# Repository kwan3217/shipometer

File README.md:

# Ansible for Shipometer

## Before first boot

Use `rpi-imager`. 

### Older `rpi-image` (<2.0.3)

1. Get an image that does Debian 12 (Bookworm) not Debian 13 (Trixie)
    * Raspberry Pi OS (Other) -> Raspberry Pi OS (Legacy, 64-bit) Lite
2. Eject MicroSD card from fluttershy and insert it in SD card reader attached to Celestia. 
3. Edit settings
    * General
      * [x] Set Hostname: `fluttershy`.local
      * [x] Set username and password:
         * Username: `chrisj`
         * Password: ******
      * [ ] Configure wireless LAN
      * [x] Set locale settings:
         * Time Zone: `America/Chicago` or as appropriate 
         * Keyboard layout: `us`
    * Services
       * [x] Enable SSH
          * ( ) Use password authentication
          * (*) Allow public-key authentication only
             * Set authorized_keys for `chrisj`: `<copy and paste from first line of /home/chrisj/.ssh/id_rsa.pub>` 
    * Options
      * [ ] Play sound when finished
      * [x] Eject media when finished
      * [ ] Enable telemetry

### Newer `rpi-image` (2.0.3)
1. Select the device type -- Raspberry Pi 5 for the current `fluttershy`
2. Raspberry Pi OS (Other) -> Raspberry Pi OS (Legacy, 64-bit) Lite
3. Insert and select the correct medium -- it is often already mounted
   as `/media/chrisj/devicename`. It is CRITICALLY IMPORTANT to get this right 
   -- check that the file size matches what is expected, and that it isn't
   one of your existing drives on the host filesystem. The check box [x] Exclude System Drives
   helps with this.
4. Set the hostname `fluttershy` not `fluttershy.local` or `fluttershy.kwansystems.org`
5. Set the capital city, time zone, and keyboard layout.
6. Set the user name `chrisj` and the password `<SECRET>`
7. Skip wifi for now
8. Enable SSH
   * ( ) Use Password Authentication
   * (*) Use public key authentication
      * Set authorized_keys for `chrisj`: `<copy and paste from first line of /home/chrisj/.ssh/id_rsa.pub>` 

### Write the image
Continue until the program writes the image on the card. Writing the image will take a few minutes.

## SSH host identity
Eject the card but then plug it back into the host. Run this:

```
sudo cp -av /mnt/big/backups/fluttershy/2025-12-15/etc/ssh/ssh_host_* /media/chrisj/rootfs/etc/ssh/
```

Edit the file `/media/chrisj/rootfs/usr/lib/raspberrypi-sys-mods/firstboot` and comment out the lines about
recalculating the host identity:
```
main () {
  get_variables

  # whiptail --infobox "Generating SSH keys..." 20 60
  # regenerate_ssh_host_keys
```

## Boot new card in Fluttershy
Eject the card again, move it back to Fluttershy, and boot it.

Unmount and remove the card from the host and install it in a powered-off or red light Raspberry Pi 5.
Start it back up and wait for it to respond to pings. The router (Megumu)
knows Fluttershy's MAC address and will assign it the known IP `192.168.217.102`
and name `fluttershy.kwansystems.org`

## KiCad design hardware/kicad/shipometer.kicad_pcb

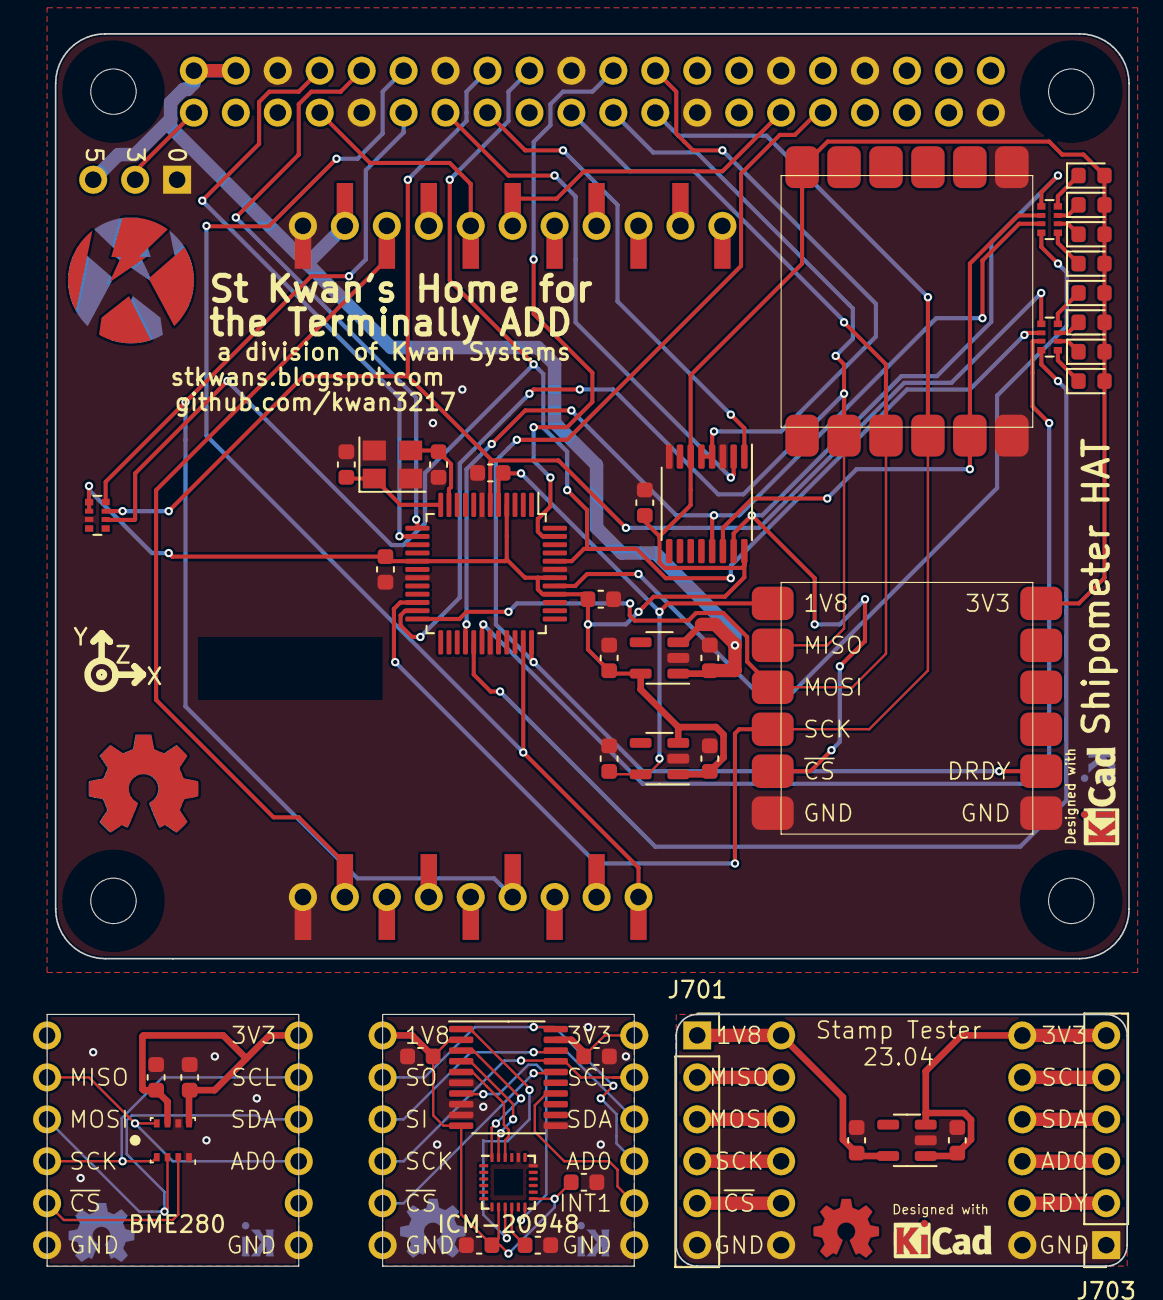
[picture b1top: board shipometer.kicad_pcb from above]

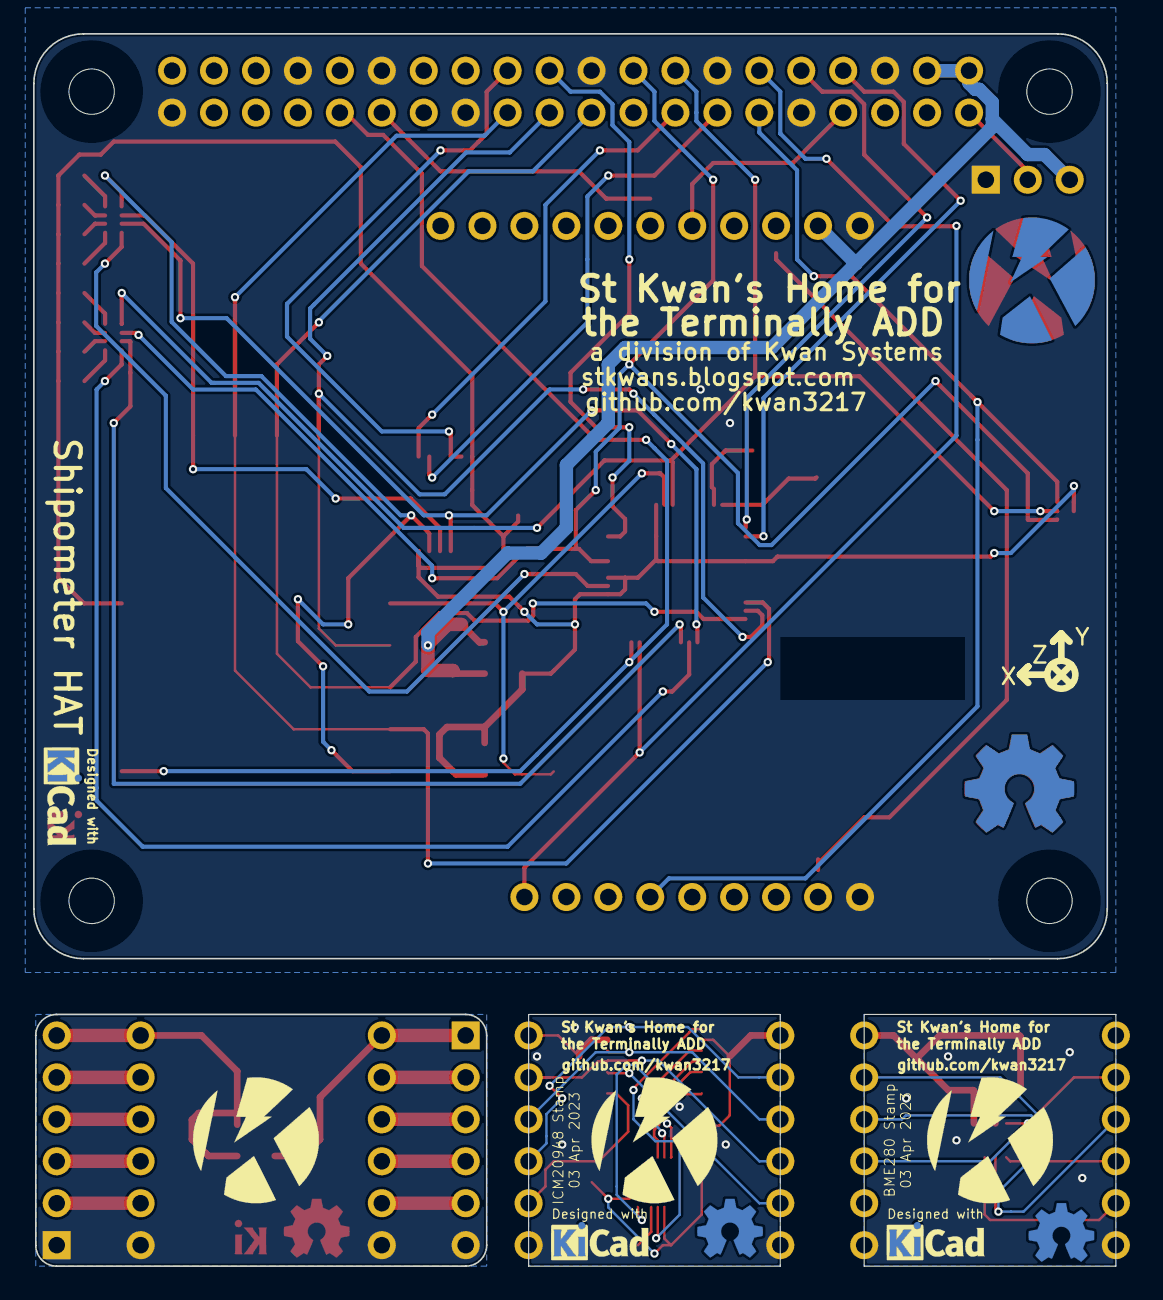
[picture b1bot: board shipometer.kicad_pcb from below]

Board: 2 copper layers, 65.5 x 74.6 mm, 66 parts (10 on the bottom side), 69 nets.

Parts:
C116, C206, C208, C401, C405, C501, C505, C605, C617, C640, C801, C805: 1uF; C_0603_1608Metric
C302, C308, C310, C313, C319: 100nF; C_0603_1608Metric
C611, C612: 22pF; C_0603_1608Metric
D101, D103, D104: White; LED_0603_1608Metric
D106: Blue; LED_0603_1608Metric
D129: Red; LED_0603_1608Metric
D130: Green; LED_0603_1608Metric
D141, D144: Yellow; LED_0603_1608Metric
G101: Axis
G102, G105: KwanSystems; StKwansSoldermask
G103, G107, G202, G302, G702: Designed with; Symbol_KiCAD-Logo_CopperAndSilkScreenTop_small
G104, G106: OSHW; OSHW-Symbol_6.7x6mm_SolderMask
G201, G301, G701: github.com/kwan3217; KWAN_CIRCLE
G203, G303, G703: OSHW; OSHW-Symbol_4x3.6mm_SolderMask
J101: Raspberry_Pi_40; PiHAT_NoSlot_Narrow
J102: Conn_01x03; PinHeader_1x03_P2.54mm_Horizontal
J104: ICM20948; StampPad
J105: BME280; StampPad
J106: ZED-F9R
J201, J301: Stamp
J701, J703: Conn_01x06_Pin; PinSocket_1x06_P2.54mm_Vertical
J702, J704: Conn_01x06_Pin; PinHeader_1x06_P2.54mm_Vertical
R101, R102: 330; R_Array_Convex_4x0402
R103: 10k; R_Array_Convex_4x0402
U102: 74LS138; TSSOP-16_4.4x5mm_P0.65mm
U201: BME280; Bosch_LGA-8_2.5x2.5mm_P0.65mm_ClockwisePinNumbering
U301: ICM-20948; InvenSense_QFN-24_3x3mm_P0.4mm
U302: TXS0108EPW; TSSOP-20_4.4x6.5mm_P0.65mm
U401: TCR2EF 3.3V; SOT-23-5
U501, U801: TCR2EF 1.8V; SOT-23-5
U601: LPC210x; LQFP-48_7x7mm_P0.5mm
Y601: 12MHz; Crystal_SMD_Abracon_ABM8G-4Pin_3.2x2.5mm

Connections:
3V3: J106.3 (3V3), J106.13 (3V3)
+1V8: C505.1, C605.1, J104.1 (1V8), U501.5 (OUT), U601.5 (VDD(1V8))
+3.3VP: J101.1 (3V3), J102.2
+3V3: C116.1, C405.1, C501.1, C617.1, C640.1, D101.2 (A), D103.2 (A), D104.2 (A), D106.2 (A), D129.2 (A), D130.2 (A), D141.2 (A), D144.2 (A), J104.12 (3V3), J105.12 (3V3), R103.1 (4), R103.2 (4), U102.6 (E3), U102.16 (VCC), U401.5 (OUT), U501.1 (IN), U501.3 (EN), U601.4 (VBAT), U601.17 (VDD(3V3)), U601.40 (VDD(3V3)), U601.42 (VDDA)
+5V: C401.1, J101.2 (5V), J101.4 (5V), J102.3, J106.2 (5V), U401.1 (IN), U401.3 (EN)
/BOOTSTRAP-: D144.1 (K), R102.7 (5)
/CS_A0: J101.15 (GPIO22_(GEN3)), U102.1 (A0)
/CS_A1: J101.13 (GPIO27_(GEN2)), U102.2 (A1)
/DRDY-: D129.1 (K), R102.5
/DRDY_6D: J101.31 (GPIO6), J104.8 (DRDY), U601.36 ((CTS1/CAP1.1/AD0.4)P0.11)
/DRDY_MAG: J101.22 (GPIO25_(GEN6)), U601.47 ((CAP1.2/SCL1)P0.17)
/DRDY_MAG-: D130.1 (K), R102.6 (5)
/GPS_RX: J101.7 ((TX3)_GPIO4), J106.5 (RX/MOSI)
/GPS_TX: J101.29 ((RX3)_GPIO5), J106.6 (TX/MISO)
/GPS_~RESET: J101.11 (GPIO17_(GEN0)), J106.17 (~RESET), R103.8 (5)
/IMU/INT1_1V8: U301.12 (INT1), U302.7 (A6)
/IMU/INT1_3V3: J301.8 (INT1), U302.14 (B6)
/IMU/MISO_1V8: U301.9 (SDO/AD0), U302.1 (A1)
/IMU/MISO_3V3: J301.2 (MISO), J301.9 (AD0), U302.20 (B1)
/IMU/MOSI_1V8: U301.24 (SDA/SDI), U302.3 (A2)
/IMU/MOSI_3V3: J301.3 (MOSI), J301.10 (SDA), U302.18 (B2)
/IMU/Q_1V8: C302.1, C308.1, C313.1, J301.1 (1V8), U301.8 (VDDIO), U301.13 (VDD), U302.2 (VCCA), U302.10 (OE)
/IMU/Q_3V3: C319.1, J301.12 (3V3), U302.19 (VCCB)
/IMU/Q_GND: C302.2, C308.2, C310.2, C313.2, C319.2, J301.6 (GND), J301.7 (GND), U301.18 (GND), U301.20 (GND), U302.6 (A5), U302.8 (A7), U302.9 (A8), U302.11 (GND)
/IMU/SCK_1V8: U301.23 (SCL/SCLK), U302.4 (A3)
/IMU/SCK_3V3: J301.4 (SCK), J301.11 (SCL), U302.17 (B3)
/IMU/~CS_1V8: U301.22 (~CS), U302.5 (A4)
/IMU/~CS_3V3: J301.5 (~CS), U302.16 (B4)
/LPC_RESET-: D106.1 (K), R102.8 (5)
/LPC_RX: J101.8 ((TX0)_GPIO14), U601.14 ((RXD0/MAT3.2)P0.1)
/LPC_TX: J101.10 ((RX0)_GPIO15), U601.13 ((TXD0/MAT3.1)P0.0)
/LPC_~BOOTSTRAP: J101.18 (GPIO24_(GEN5)), R102.2 (4), R103.6 (5), U601.44 ((DCD1/SCK1/EINT1)P0.14)
/LPC_~RESET: J101.16 (GPIO23_(GEN4)), R102.1 (4), R103.7 (5), U601.6 (~RST)
/MISO_3V3: J101.21 ((SPI_MISO)_GPIO9), J104.2 (MISO), J105.2 (MISO), U601.23 ((MISO0/MAT0.1)P0.5)
/MOSI_3V3: J101.19 ((SPI_MOSI)_GPIO10), J104.3 (MOSI), J105.3 (MOSI), U601.24 ((MOSI0/CAP0.2)P0.6)
/PPS: J101.12 (GPIO18_(GEN1)), J106.20 (PPS), U601.35 ((RTS1/CAP1.0/AD0.3)P0.10)
/PPS-: D141.1 (K), R101.5
/Pressure/MISO: J201.2 (MISO), J201.9 (AD0), U201.5 (SDO)
/Pressure/MOSI: J201.3 (MOSI), J201.10 (SDA), U201.3 (SDI)
/Pressure/Q_3V3: C206.1, C208.1, J201.12 (3V3), U201.6 (VDDIO), U201.8 (VDD)
/Pressure/Q_GND: C206.2, C208.2, J201.6 (GND), J201.7 (GND), U201.1 (GND), U201.7 (GND)
/Pressure/SCK: J201.4 (SCK), J201.11 (SCL), U201.4 (SCK)
/Pressure/~CS: J201.5 (~CS), U201.2 (CSB)
/SCK_3V3: J101.23 ((SPI_SCLK)_GPIO11), J104.4 (SCK), J105.4 (SCK), U601.22 ((SCK0/CAP0.1)P0.4)
/Stamp Tester/Q_1V8: C805.1, J701.1, J702.1, U801.5 (OUT)
/Stamp Tester/Q_3V3: C801.1, J703.6, J704.6, U801.1 (IN), U801.3 (EN)
/Stamp Tester/Q_AD0: J703.3, J704.3
/Stamp Tester/Q_DRDY: J703.2, J704.2
/Stamp Tester/Q_GND: C801.2, C805.2, J701.6, J702.6, J703.1, J704.1, U801.2 (GND)
/Stamp Tester/Q_MISO: J701.2, J702.2
/Stamp Tester/Q_MOSI: J701.3, J702.3
/Stamp Tester/Q_SCK: J701.4, J702.4
/Stamp Tester/Q_SCL: J703.5, J704.5
/Stamp Tester/Q_SDA: J703.4, J704.4
/Stamp Tester/Q_~CS: J701.5, J702.5
/Timer/XTAL1: C611.2, U601.11 (XTAL1), Y601.3
/Timer/XTAL2: C612.2, U601.12 (XTAL2), Y601.1
/~CE0: J101.24 ((~SPI_CE0)_GPIO8), U102.4 (E1), U102.5 (E2)
/~CS_6D: J104.5 (~CS), R101.1 (4), U102.15 (O0)
/~CS_6D+: D101.1 (K), R101.8 (5)
/~CS_LPC: R101.3 (4), U102.13 (O2), U601.28 ((SSEL0/MAT2.0)P0.7)
/~CS_LPC+: D104.1 (K), R101.6 (5)
/~CS_PRES: J105.5 (~CS), R101.2 (4), U102.14 (O1)
/~CS_PRES+: D103.1 (K), R101.7 (5)
/~DRDY_6D_ECHO: R102.4, U601.29 ((TXD1/MAT2.1)P0.8)
/~DRDY_MAG_ECHO: R102.3 (4), U601.30 ((RXD1/MAT2.2)P0.9)
/~PPS_ECHO: R101.4, U601.41 ((DTR1/MAT1.1)P0.13)
GND: C116.2, C401.2, C405.2, C501.2, C505.2, C605.2, C611.1, C612.1, C617.2, C640.2, J101.6 (GND), J101.9 (GND), J101.14 (GND), J101.20 (GND), J101.25 (GND), J101.30 (GND), J101.34 (GND), J101.39 (GND), J102.1, J104.6 (GND), J104.7 (GND), J105.6 (GND), J105.7 (GND), J106.1 (GND), J106.12 (GND), R103.3 (4), U102.3 (A2), U102.8 (GND), U401.2 (GND), U501.2 (GND), U601.7 (VSS), U601.19 (VSS), U601.31 (VSSA), U601.43 (VSS), Y601.2, Y601.4
unnamed: C310.1, U301.10 (REGOUT)

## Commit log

2025-12-16 Initial commit - ansible project for fluttershy
2025-12-16 Initial commit for fluttershy structure
2025-12-16 Renamed role to pps since it only covers PPS on pin 18
2025-12-17 Added GPSd role
2025-12-22 Add common handlers -- daemon reload, reload udev rules, reboot required
2025-12-22 Move uart2 overlay from pps to gpsd
2025-12-22 Remove addition of _chrony -- the chrony role handles this
2025-12-22 Add back the restart handler
2025-12-22 Try yet again to get the gpsd.socket to listen correctly
2025-12-22 Add a notification for restart gpsd
2025-12-22 Add dependencies for piaware
2025-12-22 Add task to bring up piaware
2025-12-22 Ignore pycharm stuff
2025-12-22 Create secrets folder and instructions for reconstructing it
2025-12-23 Make everything dependent on common so it always gets fully installed
2025-12-23 Add README.md which includes instructions for pre-ansible stuff
2025-12-23 Move gpsd override stuff into its own full file, instead of trying a block edit. Overrides don't seem to like comments and/or blocks.
2025-12-23 Add an sshd restart handler
2025-12-29 Change piaware id to a literal string instead of reference to file with the string
2025-12-29 Add "shipometer" (recording) tasks
2025-12-29 Make sure gpsd.socket.d folder exists
2025-12-29 Activate the "shipometer" role
2025-12-29 Remove stuff on ssh host identity -- we now ignore it while running ansible and install the old identity *with* ansible.
2025-12-29 Moved ansible into a subfolder so that the repository can be for all of shipometer
2025-12-29 Moved ansible .gitignore
2025-12-29 Reference Ralf Lange's RaspberryPiCases project to pull in mechanical scad for Raspberry Pi 5.
2025-12-29 Restructure .gitignore
2025-12-29 Added Shipometer 23.04 as built
2025-12-29 Removed separate board files -- only unified project is included.
2025-12-29 Imported shipometer hat 23.04 as built, updated to Kicad 9
2025-12-29 Add fan sandwich at v3. This is the version that is currently (2025-12-29) in the Fluttershy stack.
2025-12-29 Add svg files used for engraved logos
2025-12-29 Add scad files for zed_f9r and its own case, shipometer, and factored-out primitives.
2026-01-02 Add initial scad file for dAISy2+
2026-01-02 Add isolated file for fan sandwich
2026-01-02 Include more of the fan stack
2026-01-09 Change version number to 23.04.1 reflecting the green-wire fix
